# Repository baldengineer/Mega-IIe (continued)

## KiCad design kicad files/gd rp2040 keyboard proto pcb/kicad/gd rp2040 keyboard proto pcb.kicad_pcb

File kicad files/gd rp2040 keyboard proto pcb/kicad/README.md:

RP2040-based board to test emulating an Apple IIe keyboard

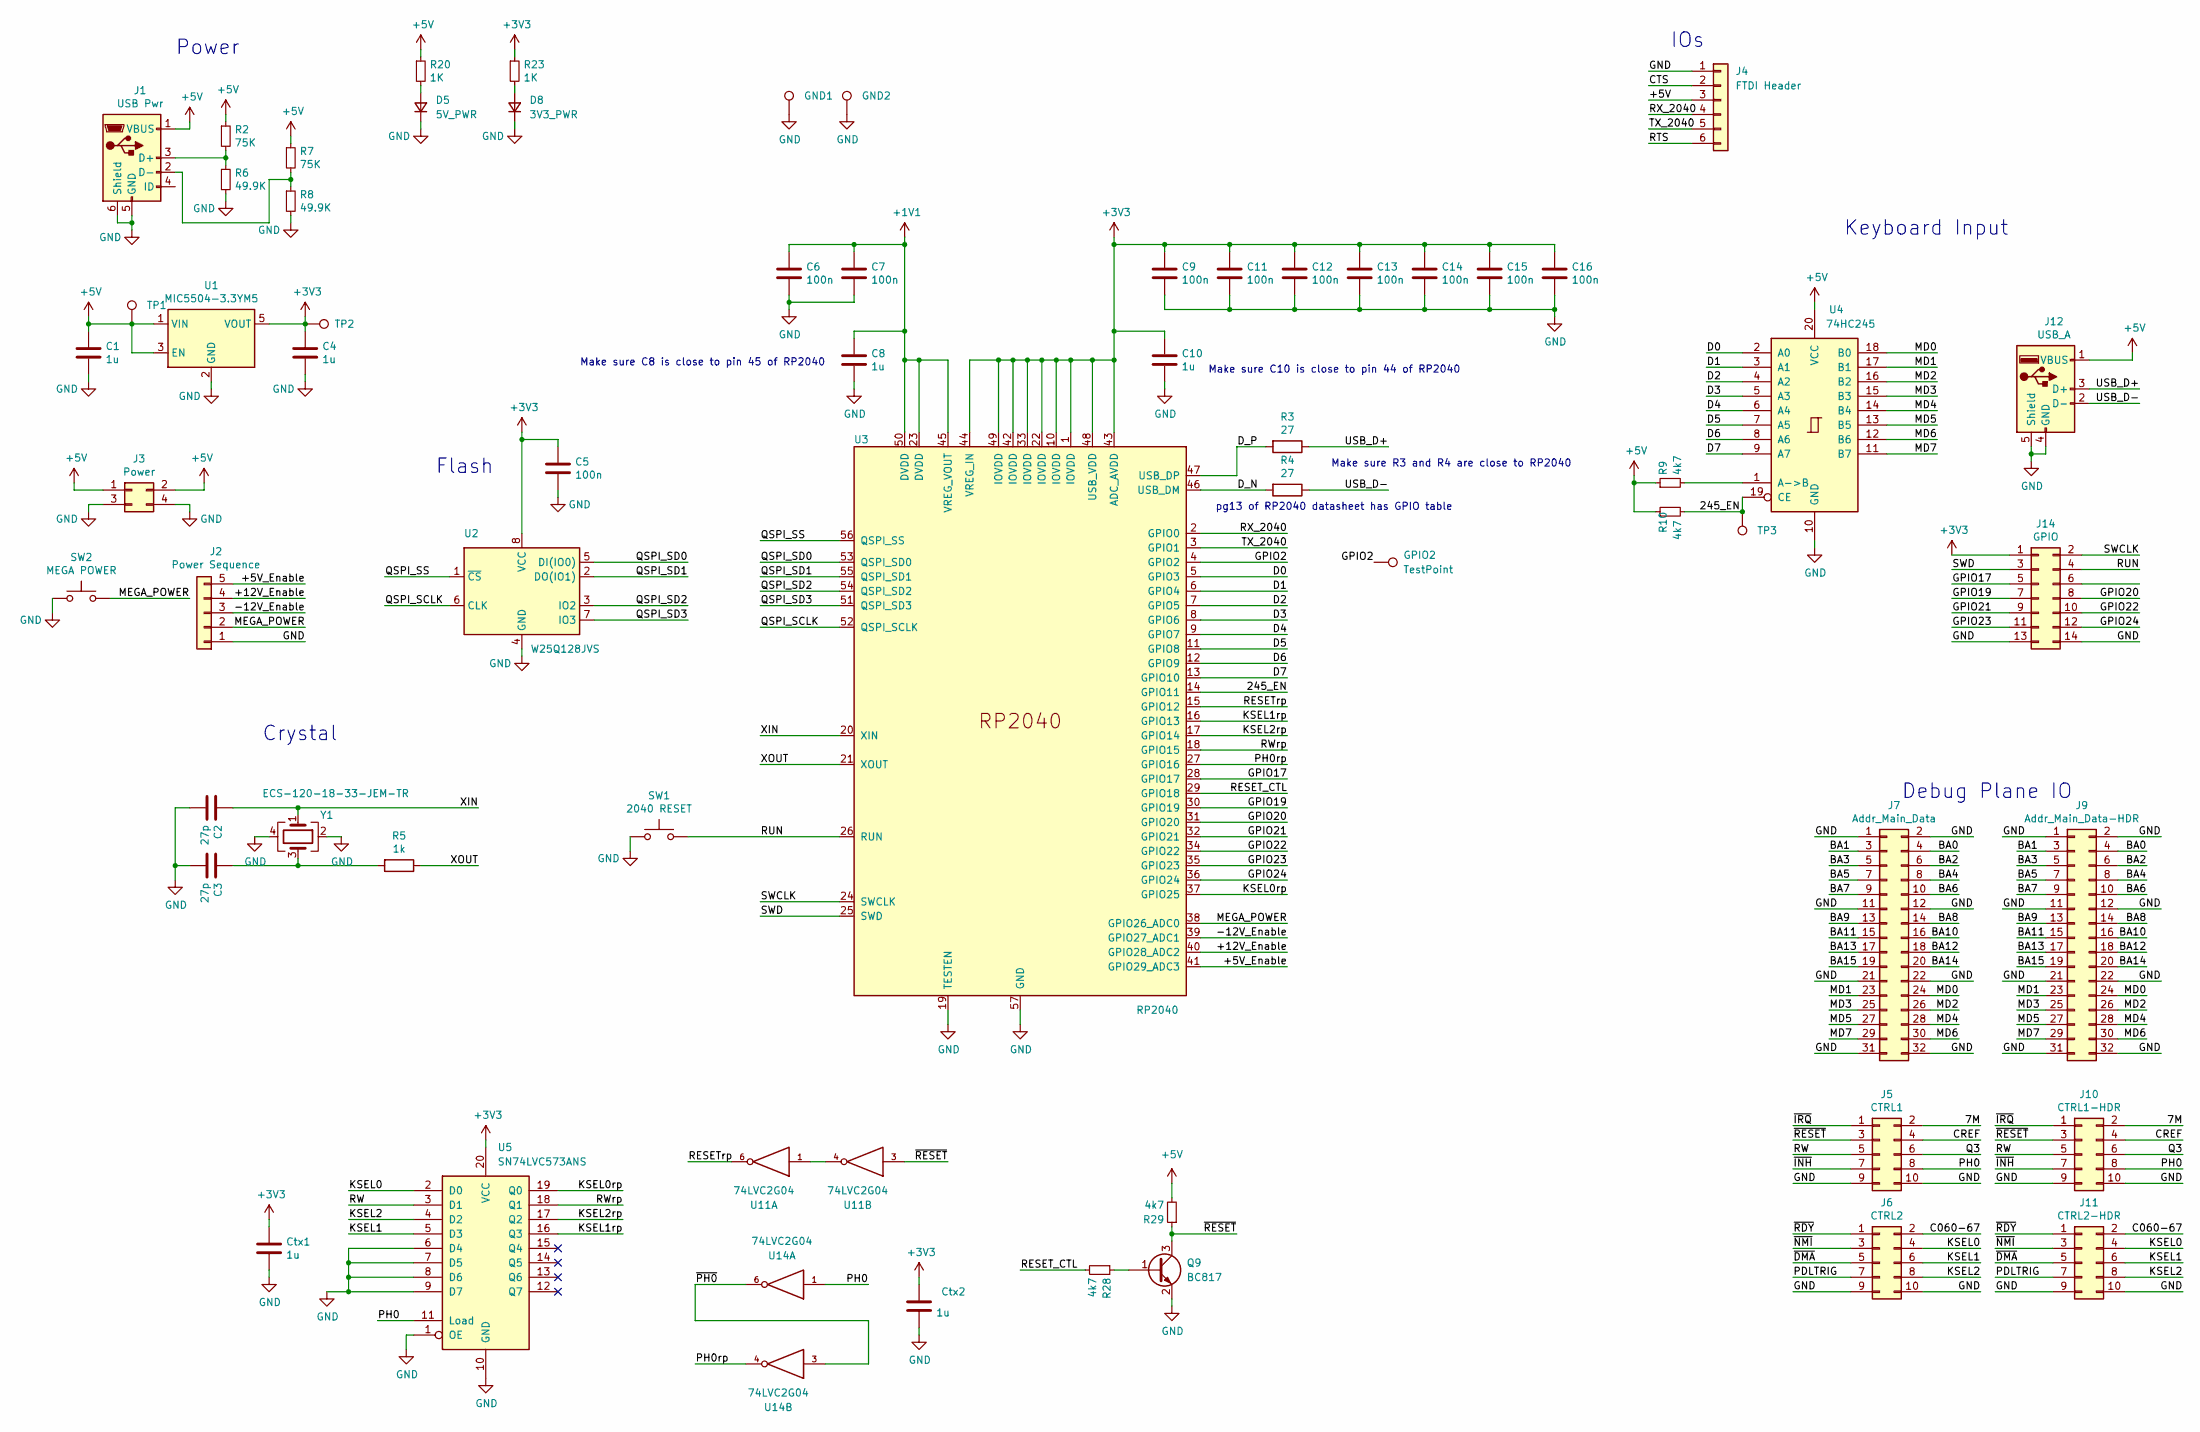
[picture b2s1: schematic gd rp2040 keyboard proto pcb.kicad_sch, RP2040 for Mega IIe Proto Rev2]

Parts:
C1, C4: 1u; C_0805_2012Metric
C2, C3: 27p; C_0603_1608Metric
C5: 100n; C_0805_2012Metric
C6, C7, C9, C11, C12, C13, C14, C15, C16: 100n; C_0603_1608Metric
C8, C10: 1u; C_0603_1608Metric
Ctx1, Ctx2: 1u; C_0603_1608Metric
D5: 5V_PWR; LED_1206_3216Metric
D8: 3V3_PWR; LED_1206_3216Metric
GND1, GND2: TestPoint_Harwin; Harwin-S1751-46-Test-Point
GPIO2: TestPoint; TestPoint_Pad_D1.0mm
J1: USB Pwr; USB_Mini-B_Wuerth_65100516121_Horizontal
J2: Power Sequence; PinSocket_1x05_P2.54mm_Vertical
J3: Power; PinSocket_2x02_P2.54mm_Vertical
J4: FTDI Header; PinSocket_1x06_P2.54mm_Vertical
J5: CTRL1; PinHeader_2x05_P2.54mm_Horizontal
J6: CTRL2; PinHeader_2x05_P2.54mm_Horizontal
J7: Addr_Main_Data; PinHeader_2x16_P2.54mm_Horizontal
J9: Addr_Main_Data-HDR; PinHeader_2x16_P2.54mm_Vertical
J10: CTRL1-HDR; PinHeader_2x05_P2.54mm_Vertical
J11: CTRL2-HDR; PinHeader_2x05_P2.54mm_Vertical
J12: USB_A; USB_A_GCT_USB1125; MPN USB1125-GF-B
J14: GPIO; PinHeader_2x07_P2.54mm_Vertical
Q9: BC817; SOT-23
R2, R7: 75K; R_0805_2012Metric
R3, R4: 27; R_0603_1608Metric
R5: 1k; R_0603_1608Metric
R6, R8: 49.9K; R_0805_2012Metric
R9, R10, R28, R29: 4k7; R_0805_2012Metric
R20, R23: 1K; R_0805_2012Metric
SW1: 2040 RESET; SW_Push_CK_PTS525_SM15
SW2: MEGA POWER; SW_Push_CK_PTS525_SM15
TP1, TP2, TP3: TestPoint_Harwin; Harwin-S1751-46-Test-Point
U1: MIC5504-3.3YM5; SOT-23-5
U2: W25Q128JVS; SOIC-8_5.23x5.23mm_P1.27mm
U3: RP2040; RP2040-QFN-56
U4: 74HC245; SOIC-20W_7.5x12.8mm_P1.27mm
U5: SN74LVC573ANS; SO-20_5.3x12.6mm_P1.27mm
U11, U14: 74LVC2G04; SOT-363_SC-70-6
Y1: ECS-120-18-33-JEM-TR; Crystal_SMD_3225-4Pin_3.2x2.5mm

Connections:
+1V1: C6.1, C7.1, C8.1, U3.23 (DVDD), U3.45 (VREG_VOUT), U3.50 (DVDD)
+3V3: C4.1, C5.1, C9.1, C10.1, C11.1, C12.1, C13.1, C14.1, C15.1, C16.1, Ctx1.1, Ctx2.1, J14.1, R23.1, TP2.1, U1.5 (VOUT), U2.8 (VCC), U3.1 (IOVDD), U3.10 (IOVDD), U3.22 (IOVDD), U3.33 (IOVDD), U3.42 (IOVDD), U3.43 (ADC_AVDD), U3.44 (VREG_IN), U3.48 (USB_VDD), U3.49 (IOVDD), U5.20 (VCC), U11.5 (+3V3), U14.5 (+3V3)
+5V: C1.1, J1.1 (VBUS), J3.1, J3.2, J4.3, J12.1 (VBUS), R2.1, R7.1, R9.1, R10.1, R20.1, R29.2, TP1.1, U1.1 (VIN), U1.3 (EN), U4.20 (VCC)
/7M: J5.2, J10.2
/245_EN: R10.2, TP3.1, U3.14 (GPIO11), U4.19 (CE)
/+5V_Enable: J2.5, U3.41 (GPIO29_ADC3)
/+12V_Enable: J2.4, U3.40 (GPIO28_ADC2)
/-12V_Enable: J2.3, U3.39 (GPIO27_ADC1)
/BA0: J7.4, J9.4
/BA1: J7.3, J9.3
/BA2: J7.6, J9.6
/BA3: J7.5, J9.5
/BA4: J7.8, J9.8
/BA5: J7.7, J9.7
/BA6: J7.10, J9.10
/BA7: J7.9, J9.9
/BA8: J7.14, J9.14
/BA9: J7.13, J9.13
/BA10: J7.16, J9.16
/BA11: J7.15, J9.15
/BA12: J7.18, J9.18
/BA13: J7.17, J9.17
/BA14: J7.20, J9.20
/BA15: J7.19, J9.19
/C060-67: J6.2, J11.2
/CREF: J5.4, J10.4
/CTS: J4.2
/D0: U3.5 (GPIO3), U4.2 (A0)
/D1: U3.6 (GPIO4), U4.3 (A1)
/D2: U3.7 (GPIO5), U4.4 (A2)
/D3: U3.8 (GPIO6), U4.5 (A3)
/D4: U3.9 (GPIO7), U4.6 (A4)
/D5: U3.11 (GPIO8), U4.7 (A5)
/D6: U3.12 (GPIO9), U4.8 (A6)
/D7: U3.13 (GPIO10), U4.9 (A7)
/D_N: R4.2, U3.46 (USB_DM)
/D_P: R3.2, U3.47 (USB_DP)
/GPIO2: GPIO2.1, U3.4 (GPIO2)
/GPIO17: J14.5, U3.28 (GPIO17)
/GPIO19: J14.7, U3.30 (GPIO19)
/GPIO20: J14.8, U3.31 (GPIO20)
/GPIO21: J14.9, U3.32 (GPIO21)
/GPIO22: J14.10, U3.34 (GPIO22)
/GPIO23: J14.11, U3.35 (GPIO23)
/GPIO24: J14.12, U3.36 (GPIO24)
/KSEL0: J6.4, J11.4, U5.2 (D0)
/KSEL0rp: U3.37 (GPIO25), U5.19 (Q0)
/KSEL1: J6.6, J11.6, U5.5 (D3)
/KSEL1rp: U3.16 (GPIO13), U5.16 (Q3)
/KSEL2: J6.8, J11.8, U5.4 (D2)
/KSEL2rp: U3.17 (GPIO14), U5.17 (Q2)
/MD0: J7.24, J9.24, U4.18 (B0)
/MD1: J7.23, J9.23, U4.17 (B1)
/MD2: J7.26, J9.26, U4.16 (B2)
/MD3: J7.25, J9.25, U4.15 (B3)
/MD4: J7.28, J9.28, U4.14 (B4)
/MD5: J7.27, J9.27, U4.13 (B5)
/MD6: J7.30, J9.30, U4.12 (B6)
/MD7: J7.29, J9.29, U4.11 (B7)
/MEGA_POWER: J2.2, SW2.2, U3.38 (GPIO26_ADC0)
/PDLTRIG: J6.7, J11.7
/PH0: J5.8, J10.8, U5.11 (Load), U14.1
/PH0rp: U3.27 (GPIO16), U14.4
/Q3: J5.6, J10.6
/QSPI_SCLK: U2.6 (CLK), U3.52 (QSPI_SCLK)
/QSPI_SD0: U2.5 (DI(IO0)), U3.53 (QSPI_SD0)
/QSPI_SD1: U2.2 (DO(IO1)), U3.55 (QSPI_SD1)
/QSPI_SD2: U2.3 (IO2), U3.54 (QSPI_SD2)
/QSPI_SD3: U2.7 (IO3), U3.51 (QSPI_SD3)
/QSPI_SS: U2.1 (~CS), U3.56 (QSPI_SS)
/RESET_CTL: R28.2, U3.29 (GPIO18)
/RESETrp: U3.15 (GPIO12), U11.6
/RTS: J4.6
/RUN: J14.4, SW1.2, U3.26 (RUN)
/RW: J5.5, J10.5, U5.3 (D1)
/RWrp: U3.18 (GPIO15), U5.18 (Q1)
/RX_2040: J4.4, U3.2 (GPIO0)
/SWCLK: J14.2, U3.24 (SWCLK)
/SWD: J14.3, U3.25 (SWD)
/TX_2040: J4.5, U3.3 (GPIO1)
/USB_D+: J12.3 (D+), R3.1
/USB_D-: J12.2 (D-), R4.1
/XIN: C2.1, U3.20 (XIN), Y1.1
/XOUT: R5.1, U3.21 (XOUT)
/~DMA: J6.5, J11.5
/~INH: J5.7, J10.7
/~IRQ: J5.1, J10.1
/~NMI: J6.3, J11.3
/~PH0: U14.3, U14.6
/~RDY: J6.1, J11.1
/~RESET: J5.3, J10.3, Q9.3 (C), R29.1, U11.3
GND: C1.2, C2.2, C3.2, C4.2, C5.2, C6.2, C7.2, C8.2, C9.2, C10.2, C11.2, C12.2, C13.2, C14.2, C15.2, C16.2, Ctx1.2, Ctx2.2, D5.1 (K), D8.1 (K), GND1.1, GND2.1, J1.5 (GND), J1.6 (Shield), J2.1, J3.3, J3.4, J4.1, J5.9, J5.10, J6.9, J6.10, J7.1, J7.2, J7.11, J7.12, J7.21, J7.22, J7.31, J7.32, J9.1, J9.2, J9.11, J9.12, J9.21, J9.22, J9.31, J9.32, J10.9, J10.10, J11.9, J11.10, J12.4 (GND), J12.5 (Shield), J14.13, J14.14, Q9.2 (E), R6.2, R8.2, SW1.1, SW2.1, U1.2 (GND), U2.4 (GND), U3.19 (TESTEN), U3.57 (GND), U4.10 (GND), U5.1 (OE), U5.6 (D4), U5.7 (D5), U5.8 (D6), U5.9 (D7), U5.10 (GND), U11.2 (GND), U14.2 (GND), Y1.2, Y1.4
unnamed: C3.1, R5.2, Y1.3
unnamed: D5.2 (A), R20.2
unnamed: D8.2 (A), R23.2
unnamed: J1.2 (D-), R7.2, R8.1
unnamed: J1.3 (D+), R2.2, R6.1
unnamed: Q9.1 (B), R28.1
unnamed: R9.2, U4.1 (A->B)
unnamed: U11.1, U11.4

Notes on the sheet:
Make sure C8 is close to pin 45 of RP2040
Crystal
Flash
IOs
pg13 of RP2040 datasheet has GPIO table
Keyboard Input
Make sure R3 and R4 are close to RP2040
Power
Make sure C10 is close to pin 44 of RP2040
Debug Plane IO

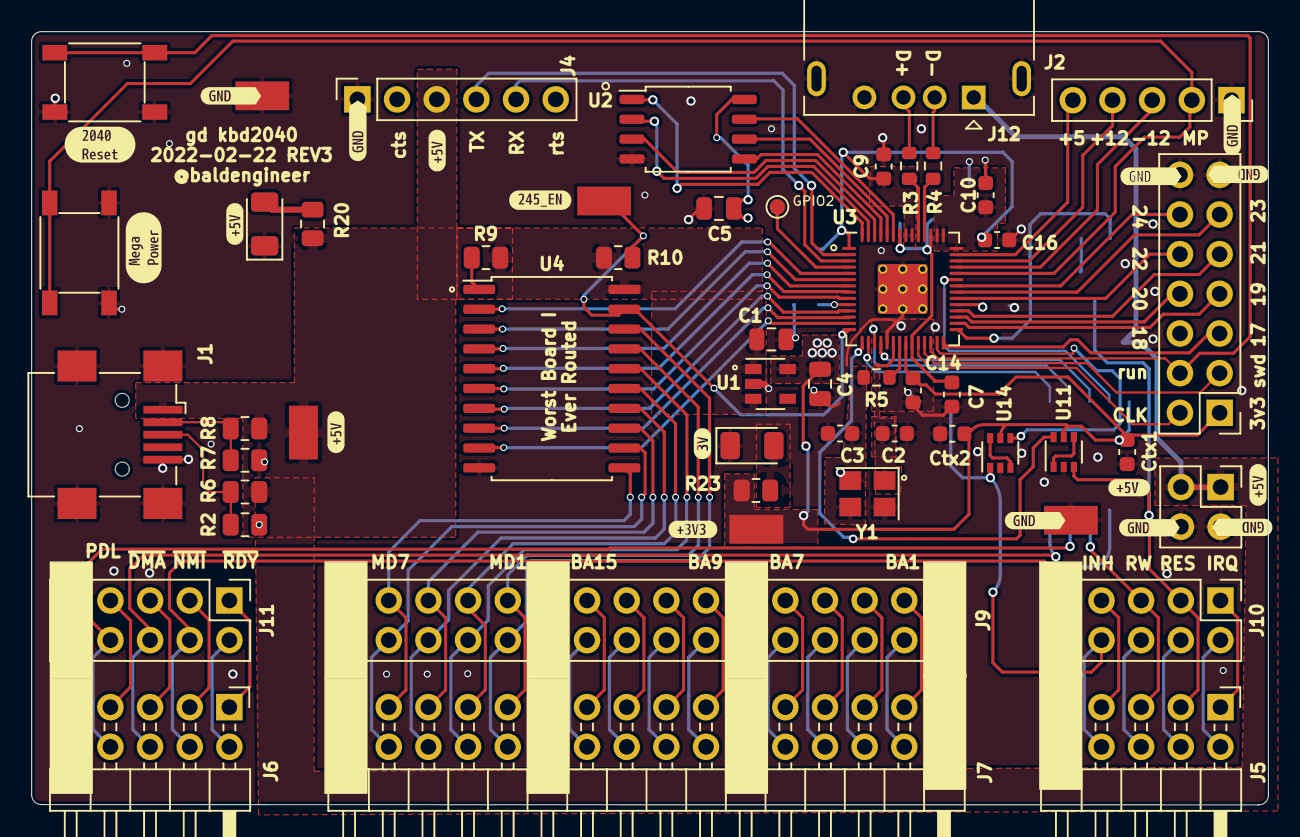
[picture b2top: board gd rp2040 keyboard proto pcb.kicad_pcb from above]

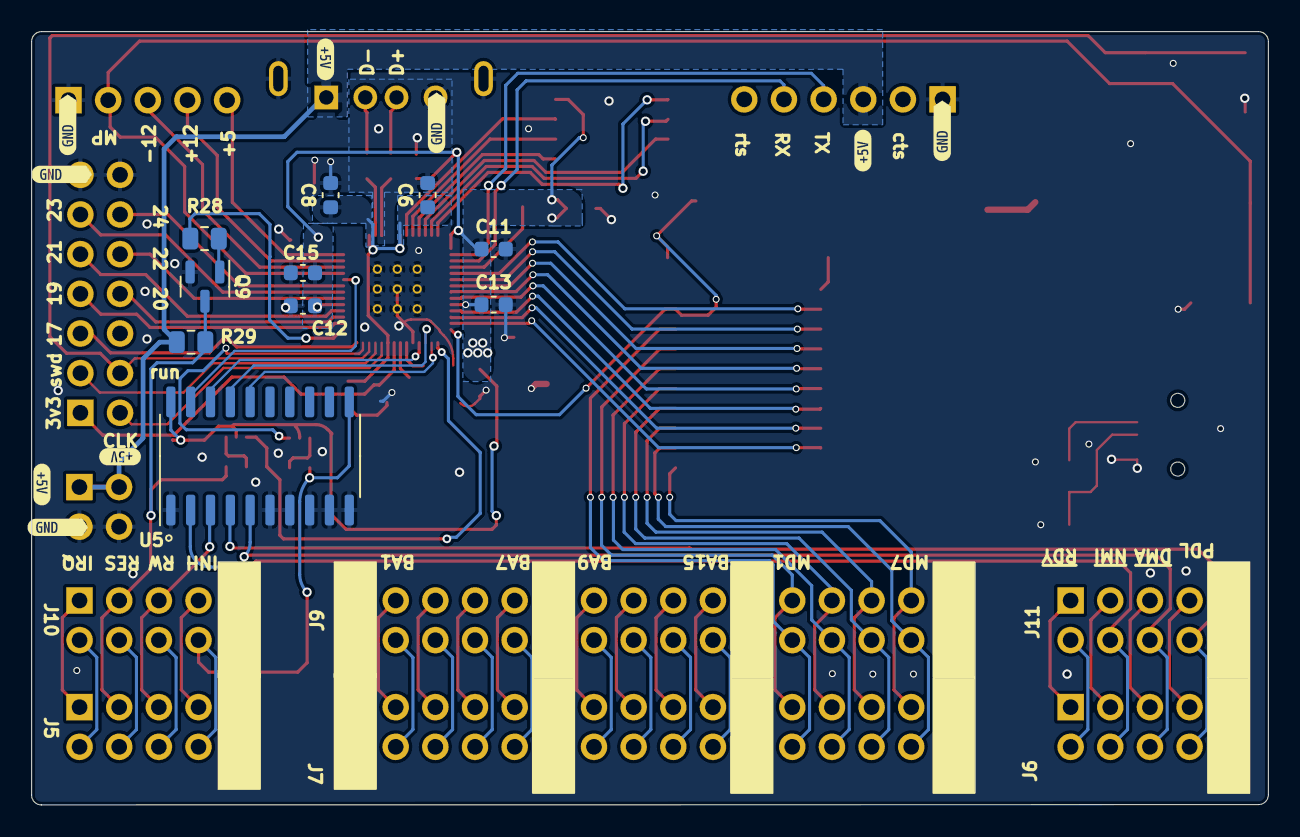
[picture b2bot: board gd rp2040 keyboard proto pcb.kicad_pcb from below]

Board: 2 copper layers, 79.2 x 49.5 mm, 90 parts (19 on the bottom side), 98 nets.

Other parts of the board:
kibuzzard-6215C1CA: G***; kibuzzard-6215C1CA
kibuzzard-62158D6B: G***; kibuzzard-62158D6B
kibuzzard-62158D92, kibuzzard-62158D92#2, kibuzzard-62158D92#3, kibuzzard-62158D92#4, kibuzzard-62158D92#5, kibuzzard-62158D92#6, kibuzzard-62158D92#7, kibuzzard-62158D92#8, kibuzzard-62158D92#9: G***; kibuzzard-62158D92
kibuzzard-62158DE7: G***; kibuzzard-62158DE7
kibuzzard-62158E3B: G***; kibuzzard-62158E3B
kibuzzard-62158E96, kibuzzard-62158E96#2, kibuzzard-62158E96#3, kibuzzard-62158E96#4, kibuzzard-62158E96#5, kibuzzard-62158E96#6, kibuzzard-62158E96#7, kibuzzard-62158E96#8, kibuzzard-62158E96#9, kibuzzard-62158E96#10, kibuzzard-62158E96#11, kibuzzard-62158E96#12, kibuzzard-62158E96#13, kibuzzard-62158E96#14: G***; kibuzzard-62158E96
kibuzzard-621593E3: G***; kibuzzard-621593E3

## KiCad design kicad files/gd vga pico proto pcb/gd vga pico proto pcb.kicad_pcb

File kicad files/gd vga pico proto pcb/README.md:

## VGA 2040 Proto PCB
The plan for this board is to take the RGBx signals from the Mega-II ASIC and attempt to turn them into a VGA output.

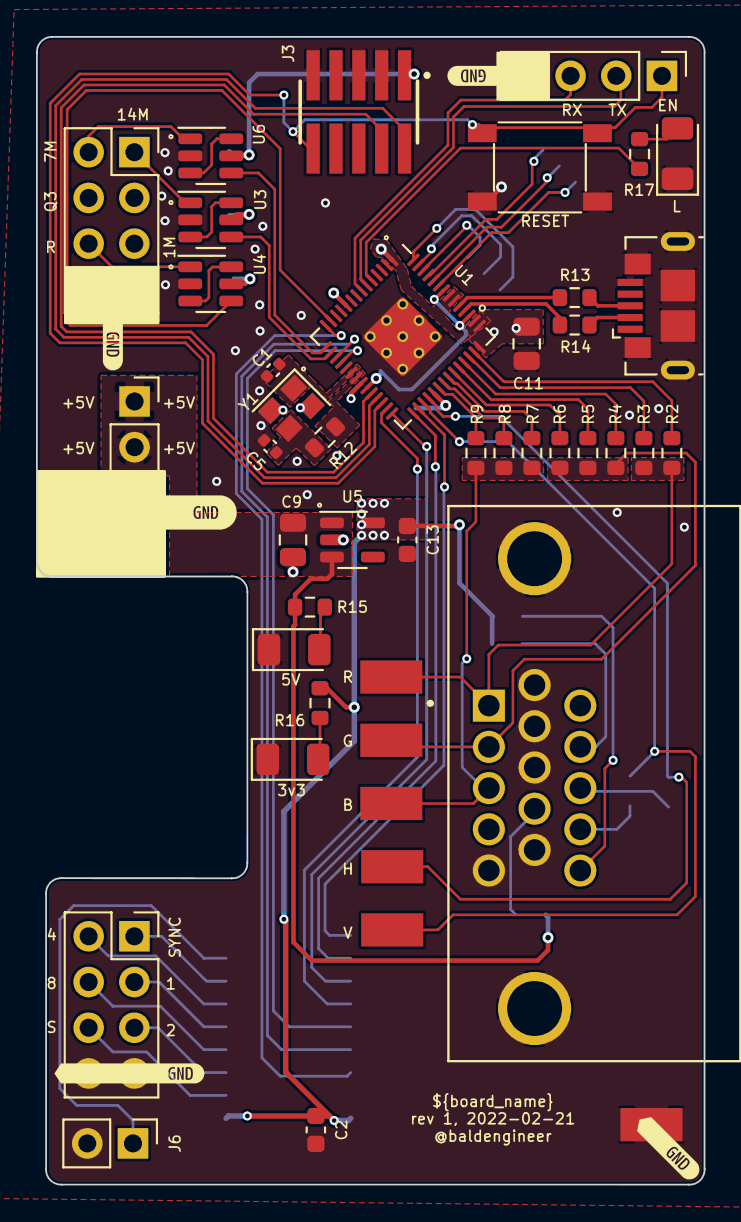
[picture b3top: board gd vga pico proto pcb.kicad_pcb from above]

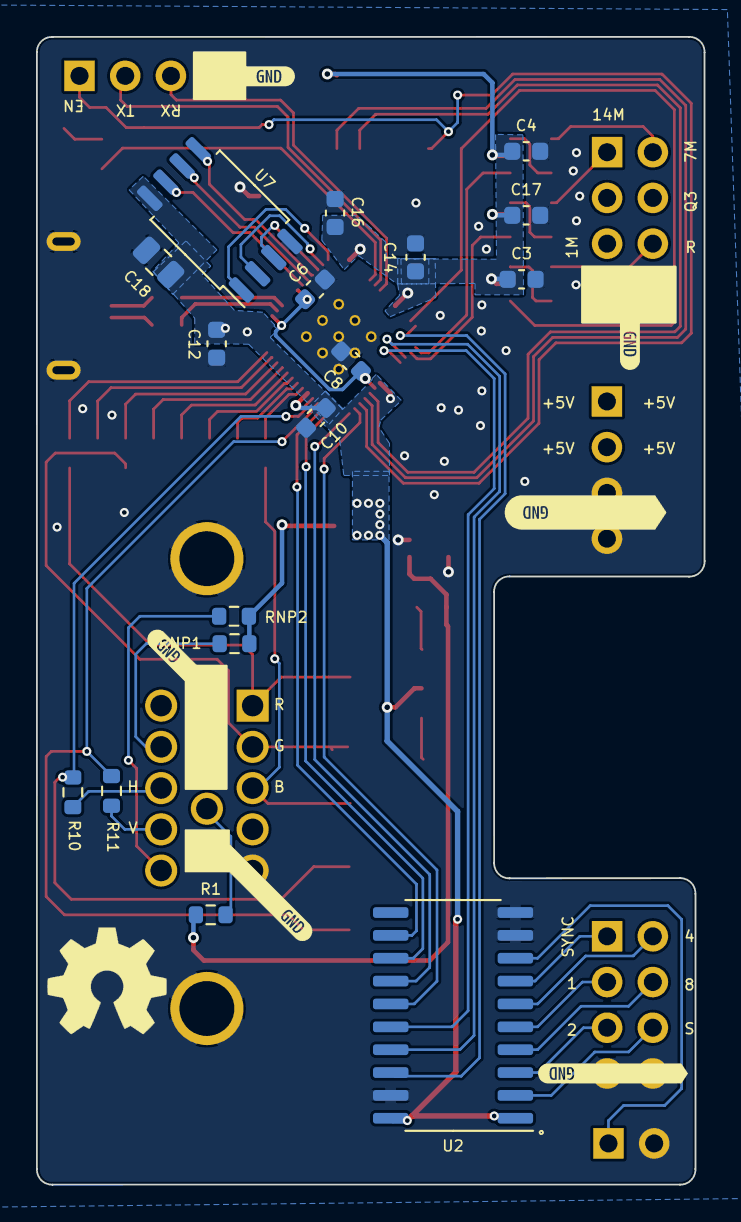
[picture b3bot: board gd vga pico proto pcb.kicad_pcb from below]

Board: 2 copper layers, 37.1 x 63.8 mm, 73 parts (23 on the bottom side), 67 nets.

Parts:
C1, C5: 6p; C_0402_1005Metric
C2, C6, C8, C10, C12, C13, C14, C16: 1u; C_0603_1608Metric
C3, C4, C17: 100n; C_0603_1608Metric
C9, C11: 10u; C_0805_2012Metric
C18: 100n; C_0805_2012Metric
D1: 5V; LED_1206_3216Metric
D2: 3V; LED_1206_3216Metric
D3: L; LED_1206_3216Metric
J1: RGB Bin; PinSocket_2x04_P2.54mm_Vertical
J2: CLKS; PinSocket_2x04_P2.54mm_Vertical
J3: SWD; SAMTEC_FTSH-105-XX-X-DV
J4: L77HDE15SD1CH4F; AMPHENOL_L77HDE15SD1CH4F
J5: VID_TXRX; PinHeader_1x04_P2.54mm_Vertical
J6: WIN; PinHeader_1x02_P2.54mm_Vertical
J7: 5V; PinSocket_1x04_P2.54mm_Vertical
J8: USB_B_Micro; USB_Micro-B_GCT_USB3076-30-A
R1, R10, R11: 100; R_0603_1608Metric
R2, R5, R8, R15, R16, R17: 1k; R_0603_1608Metric
R3: 390; R_0603_1608Metric
R4, R7: 2k2; R_0603_1608Metric
R6, R9: 470; R_0603_1608Metric
R12: 0; R_0603_1608Metric
R13, R14: 27; R_0603_1608Metric
RNP1, RNP2: 4k7; R_0603_1608Metric
SW1: 2040 RESET; SW_Push_CK_PTS525_SM15
TP2, TP3, TP4, TP5, TP6, TP7, TP8: TestPoint_Harwin; Harwin-S1751-46-Test-Point
U1: RP2040; RP2040-QFN-56
U2: 74HCT245; SO-20_5.3x12.6mm_P1.27mm
U3, U4: 74LVC2G04; SOT-23-6
U5: MIC5504-3.3YM5; SOT-23-5
U6: 74LVC2G04-DNP; SOT-23-6
U7: W25Q128JVS; SOIC-8_5.23x5.23mm_P1.27mm
Y1: ABM10AIG-12.000MHZ-7-D2Z-T; Crystal_SMD_2520-4Pin_2.5x2.0mm
kibuzzard-621468FD, kibuzzard-621468FD#2: G***; kibuzzard-621468FD
kibuzzard-621469E6, kibuzzard-621469E6#2, kibuzzard-621469E6#3, kibuzzard-621469E6#4, kibuzzard-621469E6#5, kibuzzard-621469E6#6: G***; kibuzzard-621469E6
kibuzzard-62146889, kibuzzard-62146889#2, kibuzzard-62146889#3: G***; kibuzzard-62146889

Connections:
+1V1: C6.1, C8.1, U1.23 (DVDD), U1.45 (VREG_VOUT), U1.50 (DVDD)
+3V3: C2.1, C3.1, C4.1, C10.1, C11.1, C12.1, C13.1, C14.1, C16.1, C17.1, C18.1, J3.01, R16.1, RNP1.2, RNP2.2, U1.1 (IOVDD), U1.10 (IOVDD), U1.22 (IOVDD), U1.33 (IOVDD), U1.42 (IOVDD), U1.43 (ADC_AVDD), U1.44 (VREG_IN), U1.48 (USB_VDD), U1.49 (IOVDD), U2.1 (A->B), U2.20 (VCC), U3.5 (+3V3), U4.5 (+3V3), U5.5 (VOUT), U6.5 (+3V3), U7.8 (VCC)
+5V: C9.1, J7.1, J7.2, R1.1, R15.1, U5.1 (VIN), U5.3 (EN)
/7M: J2.2, U6.1
/7M_RP: U1.15 (GPIO12), U6.4
/14M: J2.1, U3.1
/14M_RP: U1.16 (GPIO13), U3.4
/BLU0: R7.2, U1.36 (GPIO24)
/BLU1: R8.2, U1.35 (GPIO23)
/BLU2: R9.2, U1.34 (GPIO22)
/D_N: R14.2, U1.46 (USB_DM)
/D_P: R13.2, U1.47 (USB_DP)
/GRN0: R4.2, U1.39 (GPIO27_ADC1)
/GRN1: R5.2, U1.38 (GPIO26_ADC0)
/GRN2: R6.2, U1.37 (GPIO25)
/HSYNC: R10.2, TP2.1, U1.32 (GPIO21)
/LED_L: R17.1, U1.5 (GPIO3)
/QSPI_SCLK: U1.52 (QSPI_SCLK), U7.6 (CLK)
/QSPI_SD0: U1.53 (QSPI_SD0), U7.5 (DI(IO0))
/QSPI_SD1: U1.55 (QSPI_SD1), U7.2 (DO(IO1))
/QSPI_SD2: U1.54 (QSPI_SD2), U7.3 (IO2)
/QSPI_SD3: U1.51 (QSPI_SD3), U7.7 (IO3)
/QSPI_SS: U1.56 (QSPI_SS), U7.1 (~CS)
/RED0: R2.2, U1.41 (GPIO29_ADC3)
/RED1: R3.2, U1.40 (GPIO28_ADC2)
/RGB1: J1.3, U2.5 (A3)
/RGB1_RP: U1.18 (GPIO15), U2.16 (B2)
/RGB2: J1.5, U2.3 (A1)
/RGB2_RP: U1.17 (GPIO14), U2.17 (B1)
/RGB4: J1.2, U2.6 (A4)
/RGB4_RP: U1.28 (GPIO17), U2.14 (B4)
/RGB8: J1.4, U2.4 (A2)
/RGB8_RP: U1.27 (GPIO16), U2.15 (B3)
/SERVIDEO: J1.6, U2.2 (A0)
/SERVID_RP: U1.14 (GPIO11), U2.18 (B0)
/SWCLK: J3.04, U1.24 (SWCLK)
/SWDIO: J3.02, U1.25 (SWD)
/USB_D+: J8.3 (D+), R13.1
/USB_D-: J8.2 (D-), R14.1
/VGA_B: J4.3, R7.1, R8.1, R9.1, TP8.1
/VGA_G: J4.2, R4.1, R5.1, R6.1, TP7.1
/VGA_R: J4.1, R2.1, R3.1, TP6.1
/VGA_SCL: J4.15, RNP2.1
/VGA_SDA: J4.12, RNP1.1
/VID_EN: J3.10, J5.1, SW1.2, U1.26 (RUN)
/VID_RX: J5.3, U1.7 (GPIO5)
/VID_TX: J5.2, U1.6 (GPIO4)
/VSYNC: R11.2, TP3.1, U1.31 (GPIO20)
/XIN: C1.1, U1.20 (XIN), Y1.1
/XOUT: R12.1, U1.21 (XOUT)
/~RESET_RP: U1.13 (GPIO10), U4.4
/~RESET: J2.6, U4.1
/~SYNC_RP: U1.29 (GPIO18), U2.13 (B5)
/~SYNC: J1.1, U2.7 (A5)
/~WINDOW_RP: U1.30 (GPIO19), U2.12 (B6)
/~WINDOW: J6.1, U2.8 (A6)
GND: C1.2, C2.2, C3.2, C4.2, C5.2, C6.2, C8.2, C9.2, C10.2, C11.2, C12.2, C13.2, C14.2, C16.2, C17.2, C18.2, D1.1 (K), D2.1 (K), D3.1 (K), J1.7, J1.8, J2.7, J2.8, J3.03, J3.05, J3.09, J4.0, J4.5, J4.6, J4.7, J4.8, J4.10, J5.4, J6.2, J7.3, J7.4, J8.5 (GND), J8.6 (Shield), SW1.1, TP4.1, TP5.1, U1.19 (TESTEN), U1.57 (GND), U2.9 (A7), U2.10 (GND), U2.19 (CE), U3.2 (GND), U4.2 (GND), U5.2 (GND), U6.2 (GND), U7.4 (GND), Y1.2, Y1.4
unnamed: C5.1, R12.2, Y1.3
unnamed: D1.2 (A), R15.2
unnamed: D2.2 (A), R16.2
unnamed: D3.2 (A), R17.2
unnamed: J4.9, R1.2
unnamed: J4.13, R10.1
unnamed: J4.14, R11.1
unnamed: U3.3, U3.6
unnamed: U4.3, U4.6
unnamed: U6.3, U6.6

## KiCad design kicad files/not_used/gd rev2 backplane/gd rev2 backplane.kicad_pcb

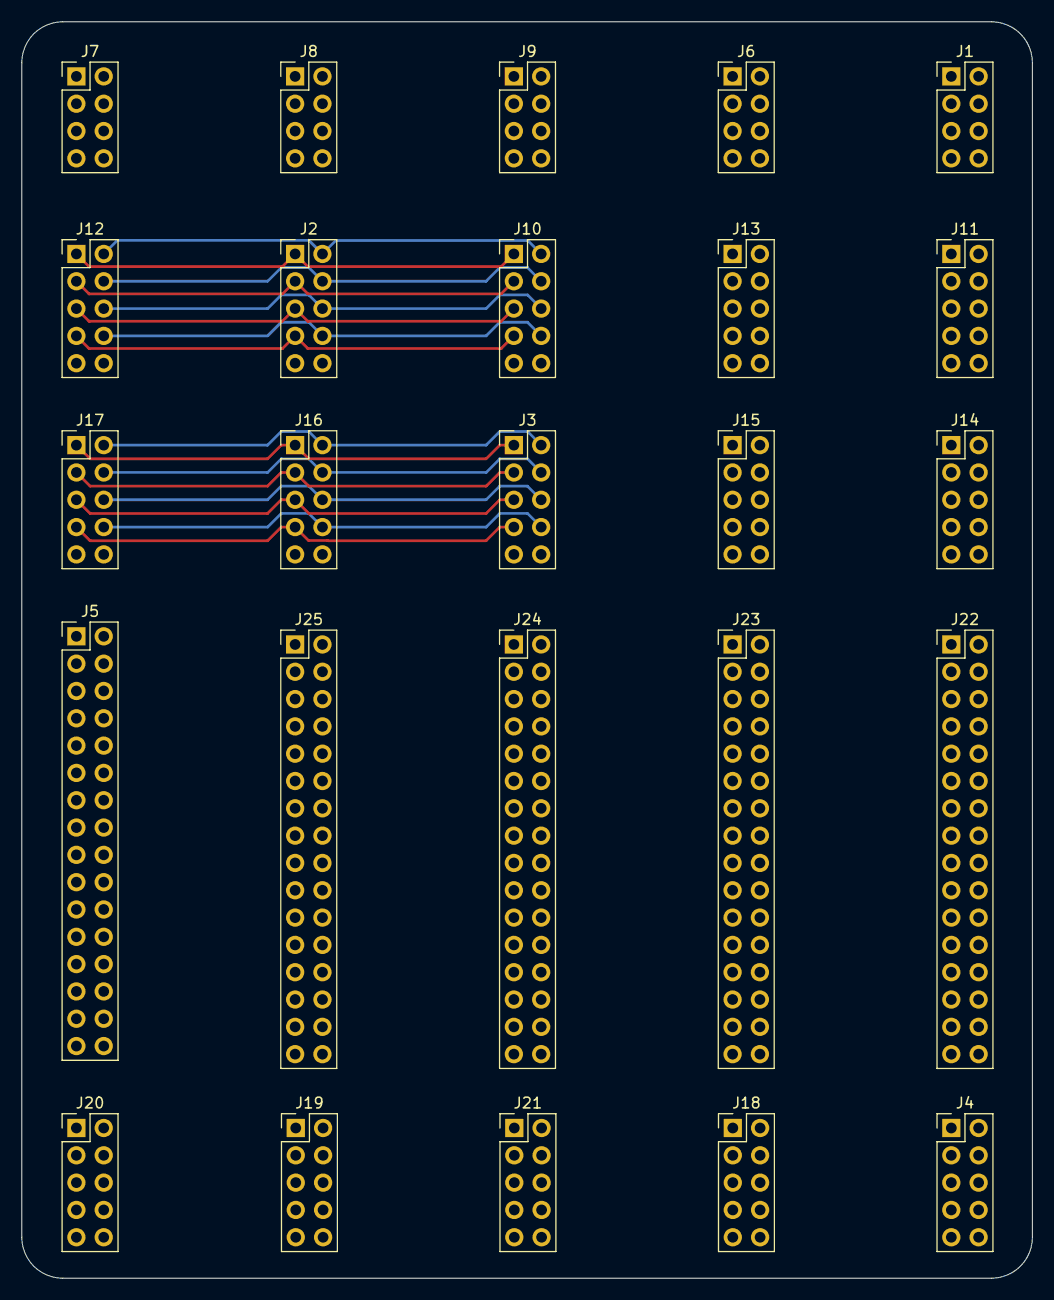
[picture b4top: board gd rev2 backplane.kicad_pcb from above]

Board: 2 copper layers, 94.0 x 116.8 mm, 25 parts (0 on the bottom side), 52 nets.

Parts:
J1, J6, J7, J8, J9: Pwr; PinHeader_2x04_P2.54mm_Vertical
J2, J10, J11, J12, J13: Slot_Maker; PinHeader_2x05_P2.54mm_Vertical
J3, J14, J15, J16, J17: CTRL2; PinHeader_2x05_P2.54mm_Vertical
J4, J18, J19, J20, J21: CTRL1; PinHeader_2x05_P2.54mm_Vertical
J5, J22, J23, J24, J25: Addr_Main_Data; PinHeader_2x16_P2.54mm_Vertical

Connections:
+5V: J1.1, J1.3, J6.1, J6.3, J7.1, J7.3, J8.1, J8.3, J9.1, J9.3
+12V: J1.5, J1.7, J6.5, J6.7, J7.5, J7.7, J8.5, J8.7, J9.5, J9.7
-12V: J1.6, J1.8, J6.6, J6.8, J7.6, J7.8, J8.6, J8.8, J9.6, J9.8
/7M: J4.2, J18.2, J19.2, J20.2, J21.2
/!DMA: J3.5, J14.5, J15.5, J16.5, J17.5
/BA0: J5.4, J22.4, J23.4, J24.4, J25.4
/BA1: J5.3, J22.3, J23.3, J24.3, J25.3
/BA2: J5.6, J22.6, J23.6, J24.6, J25.6
/BA3: J5.5, J22.5, J23.5, J24.5, J25.5
/BA4: J5.8, J22.8, J23.8, J24.8, J25.8
/BA5: J5.7, J22.7, J23.7, J24.7, J25.7
/BA6: J5.10, J22.10, J23.10, J24.10, J25.10
/BA7: J5.9, J22.9, J23.9, J24.9, J25.9
/BA8: J5.14, J22.14, J23.14, J24.14, J25.14
/BA9: J5.13, J22.13, J23.13, J24.13, J25.13
/BA10: J5.16, J22.16, J23.16, J24.16, J25.16
/BA11: J5.15, J22.15, J23.15, J24.15, J25.15
/BA12: J5.18, J22.18, J23.18, J24.18, J25.18
/BA13: J5.17, J22.17, J23.17, J24.17, J25.17
/BA14: J5.20, J22.20, J23.20, J24.20, J25.20
/BA15: J5.19, J22.19, J23.19, J24.19, J25.19
/C060-67: J3.2, J14.2, J15.2, J16.2, J17.2
/CREF: J4.4, J18.4, J19.4, J20.4, J21.4
/GND: J1.2, J1.4, J2.9, J2.10, J3.9, J3.10, J4.9, J4.10, J5.1, J5.2, J5.11, J5.12, J5.21, J5.22, J5.31, J5.32, J6.2, J6.4, J7.2, J7.4, J8.2, J8.4, J9.2, J9.4, J10.9, J10.10, J11.9, J11.10, J12.9, J12.10, J13.9, J13.10, J14.9, J14.10, J15.9, J15.10, J16.9, J16.10, J17.9, J17.10, J18.9, J18.10, J19.9, J19.10, J20.9, J20.10, J21.9, J21.10, J22.1, J22.2, J22.11, J22.12, J22.21, J22.22, J22.31, J22.32, J23.1, J23.2, J23.11, J23.12, J23.21, J23.22, J23.31, J23.32, J24.1, J24.2, J24.11, J24.12, J24.21, J24.22, J24.31, J24.32, J25.1, J25.2, J25.11, J25.12, J25.21, J25.22, J25.31, J25.32
/INTDEV6: J2.8, J10.8, J11.8, J12.8, J13.8
/KSEL0: J3.4, J14.4, J15.4, J16.4, J17.4
/KSEL1: J3.6, J14.6, J15.6, J16.6, J17.6
/KSEL2: J3.8, J14.8, J15.8, J16.8, J17.8
/MD0: J5.24, J22.24, J23.24, J24.24, J25.24
/MD1: J5.23, J22.23, J23.23, J24.23, J25.23
/MD2: J5.26, J22.26, J23.26, J24.26, J25.26
/MD3: J5.25, J22.25, J23.25, J24.25, J25.25
/MD4: J5.28, J22.28, J23.28, J24.28, J25.28
/MD5: J5.27, J22.27, J23.27, J24.27, J25.27
/MD6: J5.30, J22.30, J23.30, J24.30, J25.30
/MD7: J5.29, J22.29, J23.29, J24.29, J25.29
/MDI-MDO: J2.7, J10.7, J11.7, J12.7, J13.7
/PDLTRIG: J3.7, J14.7, J15.7, J16.7, J17.7
/PH0: J4.8, J18.8, J19.8, J20.8, J21.8
/Q3: J4.6, J18.6, J19.6, J20.6, J21.6
/RW: J4.5, J18.5, J19.5, J20.5, J21.5
/S0: J2.2, J10.2, J11.2, J12.2, J13.2
/S1: J2.1, J10.1, J11.1, J12.1, J13.1
/S2: J2.4, J10.4, J11.4, J12.4, J13.4
/S3: J2.3, J10.3, J11.3, J12.3, J13.3
/S4: J2.6, J10.6, J11.6, J12.6, J13.6
/S5: J2.5, J10.5, J11.5, J12.5, J13.5
/~INH: J4.7, J18.7, J19.7, J20.7, J21.7
/~IRQ: J4.1, J18.1, J19.1, J20.1, J21.1
/~NMI: J3.3, J14.3, J15.3, J16.3, J17.3
/~RDY: J3.1, J14.1, J15.1, J16.1, J17.1
/~RESET: J4.3, J18.3, J19.3, J20.3, J21.3

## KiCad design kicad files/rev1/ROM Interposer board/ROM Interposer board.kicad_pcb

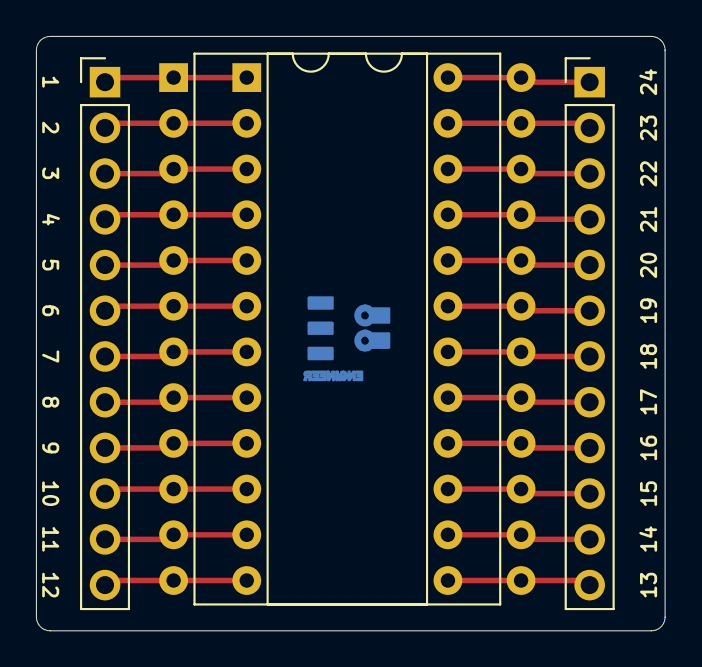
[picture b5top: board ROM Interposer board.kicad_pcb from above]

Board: 2 copper layers, 34.9 x 33.0 mm, 5 parts (1 on the bottom side), 24 nets.

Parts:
J1: IIe-Socket; DIP-24_W15.24mm
J2: ROM-Socket; DIP-24_W15.24mm
J3, J4: Conn_01x12; PinHeader_1x12_P2.54mm_Vertical
svg2mod: G***; BE5v2

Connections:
/Pin1: J1.1, J2.1, J3.1
/Pin2: J1.2, J2.2, J3.2
/Pin3: J1.3, J2.3, J3.3
/Pin4: J1.4, J2.4, J3.4
/Pin5: J1.5, J2.5, J3.5
/Pin6: J1.6, J2.6, J3.6
/Pin7: J1.7, J2.7, J3.7
/Pin8: J1.8, J2.8, J3.8
/Pin9: J1.9, J2.9, J3.9
/Pin10: J1.10, J2.10, J3.10
/Pin11: J1.11, J2.11, J3.11
/Pin12: J1.12, J2.12, J3.12
/Pin13: J1.13, J2.13, J4.12
/Pin14: J1.14, J2.14, J4.11
/Pin15: J1.15, J2.15, J4.10
/Pin16: J1.16, J2.16, J4.9
/Pin17: J1.17, J2.17, J4.8
/Pin18: J1.18, J2.18, J4.7
/Pin19: J1.19, J2.19, J4.6
/Pin20: J1.20, J2.20, J4.5
/Pin21: J1.21, J2.21, J4.4
/Pin22: J1.22, J2.22, J4.3
/Pin23: J1.23, J2.23, J4.2
/Pin24: J1.24, J2.24, J4.1
